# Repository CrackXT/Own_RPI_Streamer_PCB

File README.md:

# Own_RPI_Streamer_PCB

PCB files for RPI Streamer Board

# Description

This is a main board to hold a Raspberry Pi (4) and the Hifyberry Digi2 Pro expansion board. This puts the connections I need (for me) on one side to be able to build my own streamer.

- Part 1

The internal "power supply" (Pololu S13V30F5) delivers at 5V@3A, sensor and RGB are control by part 2.

There is a temperature sensor (Sensirion SHT45) under the SoC and an additional unregulated fan connector (e.g. Noctua NF-A4x20 5V). In addition there is the possibility to connect a lighting (RGB). Furthermore, the following connections are available... USB-C (power supply), USB-A 3.0 (data, e.g. USB stick with music on it), main switch, QWIIC/StemmaQT (sensor) and an external 5V connector (for part 2).

The board can be produced here (AISLER) with the files (.brd and .sch) or by any other PCB manufacturer. -> https://aisler.net/

# Spec

Vin: 2.8 - 22V<br>
Vout: 5V (typ., min.4,85V, max.5,15V)<br>
Iout: 3A<br>

# Serie

- .pro

# Layout

Top<br>

Bottom<br>

Routing/Dimensions(mm)<br>

Schematic<br>
Schematic as .pdf at the top of the page.

# License

Open hardware, use it, mod it, whatever you want, feel free...

# Thanks!

Own design and layout.

# Version - Build

v1.4 - 06.11.2023

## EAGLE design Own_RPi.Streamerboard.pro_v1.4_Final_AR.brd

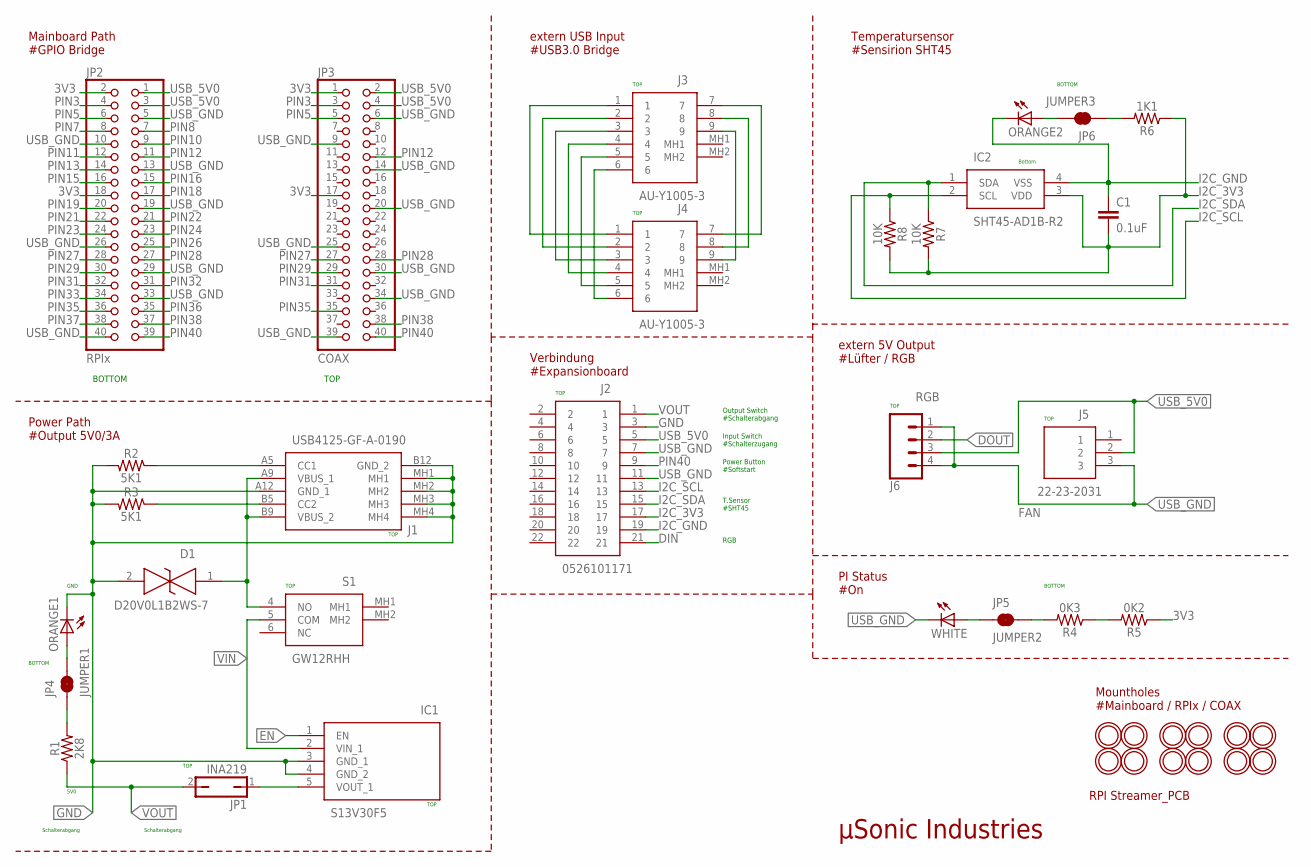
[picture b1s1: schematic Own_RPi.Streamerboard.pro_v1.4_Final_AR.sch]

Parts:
C1: 0.1uF; 0805
D1: D20V0L1B2WS-7; SOD2513X120N
IC1: S13V30F5
IC2: SHT45-AD1B-R2; SHT45AD1BR2
J1: USB4125-GF-A-0190; USB4125GFA0190
J2: 0526101171
J3, J4: AU-Y1005-3; AUY10053
J5: 22-23-2031; SHDR3W82P0X254_1X3_747X635X818
J6: CONN_041X04_NO_SILK; 1X04_NO_SILK
JP1: INA219; 1X02_NO_SILK
JP2: RPIx; 2X20-BIG
JP3: COAX; 2X20-BIG
JP4: JUMPER1; SMT-JUMPER_2_NC_TRACE_SILK
JP5: JUMPER2; SMT-JUMPER_2_NC_TRACE_SILK
JP6: JUMPER3; SMT-JUMPER_2_NC_TRACE_SILK
ORANGE1, ORANGE2: LEDCHIPLED_0805; CHIPLED_0805
R1: 2K8; 0805
R2, R3: 5K1; 0805
R4: 0K3; 0805
R5: 0K2; 0805
R6: 1K1; 0805
R7, R8: 10K; 0805
S1: GW12RHH
U$4, U$5, U$6, U$7, U$8, U$10, U$11, U$13, U$14, U$15, U$16, U$17: MOUNTINGHOLE2.5; MOUNTINGHOLE_2.5_PLATED
WHITE: LEDCHIPLED_0805; CHIPLED_0805

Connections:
3V3: JP2.2, JP2.18, JP3.1, JP3.17, R5.1
DIN: J2.21
DOUT: J6.2
EN: IC1.1 (EN)
GND: D1.2, IC1.3 (GND_1), IC1.4 (GND_2), J1.A12 (GND_1), J1.B12 (GND_2), J1.MH1, J1.MH2, J1.MH3, J1.MH4, J2.3, ORANGE1.C, R2.2, R3.2
I2C_3V3: C1.2, IC2.3 (VDD), J2.17, R6.1, R7.2, R8.2
I2C_GND: C1.1, IC2.4 (VSS), J2.19, ORANGE2.C
I2C_SCL: IC2.2 (SCL), J2.13, R8.1
I2C_SDA: IC2.1 (SDA), J2.15, R7.1
unnamed: JP4.1, R1.2
unnamed: R4.1, R5.2
unnamed: J1.B5 (CC2), R3.1
unnamed: J1.A5 (CC1), R2.1
unnamed: J3.4, J4.4
unnamed: JP6.2, ORANGE2.A
unnamed: JP5.1, WHITE.A
unnamed: IC1.5 (VOUT_1), JP1.1
unnamed: JP4.2, ORANGE1.A
unnamed: JP5.2, R4.2
unnamed: JP6.1, R6.2
unnamed: J3.6, J4.6
unnamed: J3.5, J4.5
unnamed: J3.3, J4.3
unnamed: J3.2, J4.2
unnamed: J3.1, J4.1
unnamed: J3.9, J4.9
unnamed: J3.8, J4.8
unnamed: J3.7, J4.7
PIN3: JP2.4, JP3.3
PIN5: JP2.6, JP3.5
PIN7: JP2.8
PIN8: JP2.7
PIN10: JP2.9
PIN11: JP2.12
PIN12: JP2.11, JP3.12
PIN13: JP2.14
PIN15: JP2.16
PIN16: JP2.15
PIN18: JP2.17
PIN19: JP2.20
PIN21: JP2.22
PIN22: JP2.21
PIN23: JP2.24
PIN24: JP2.23
PIN26: JP2.25
PIN27: JP2.28, JP3.27
PIN28: JP2.27, JP3.28
PIN29: JP2.30, JP3.29
PIN31: JP2.32, JP3.31
PIN32: JP2.31
PIN33: JP2.34
PIN35: JP2.36, JP3.35
PIN36: JP2.35
PIN37: JP2.38
PIN38: JP2.37, JP3.38
PIN40: J2.9, JP2.39, JP3.40
USB_5V0: J2.5, J5.2, J6.3, JP2.1, JP2.3, JP3.2, JP3.4
USB_GND: J2.7, J2.11, J5.3, J6.1, J6.4, JP2.5, JP2.10, JP2.13, JP2.19, JP2.26, JP2.29, JP2.33, JP2.40, JP3.6, JP3.9, JP3.14, JP3.20, JP3.25, JP3.30, JP3.34, JP3.39, WHITE.C
VBUS_VIN: D1.1, J1.A9 (VBUS_1), J1.B9 (VBUS_2), S1.4 (NO)
VIN: IC1.2 (VIN_1), S1.5 (COM)
VOUT: J2.1, JP1.2, R1.1

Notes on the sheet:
µSonic Industries
RPI Streamer_PCB
Power Path #Output 5V0/3A
TOP
Schalterabgang
BOTTOM
Mountholes #Mainboard / RPIx / COAX
GND
5V0
Temperatursensor #Sensirion SHT45
extern 5V Output #Lüfter / RGB
extern USB Input #USB3.0 Bridge
Mainboard Path #GPIO Bridge
PI Status #On
RGB
Bottom
Power Button #Softstart
Output Switch #Schalterabgang
Input Switch #Schalterzugang
T.Sensor #SHT45
Verbindung #Expansionboard
FAN

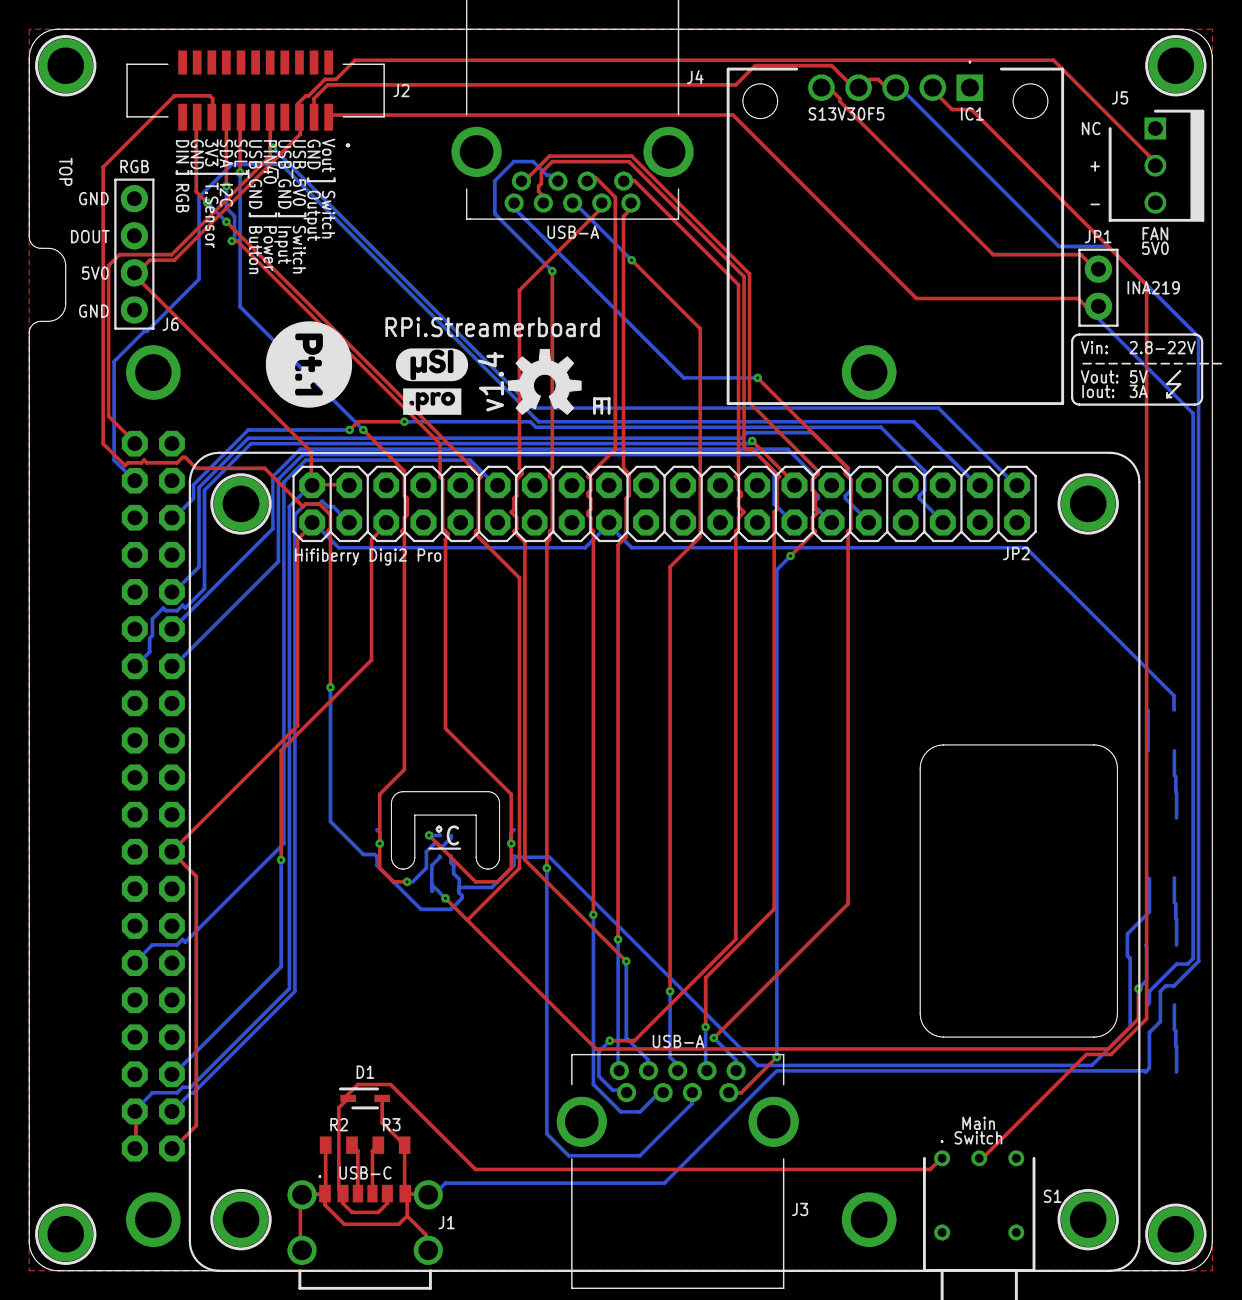
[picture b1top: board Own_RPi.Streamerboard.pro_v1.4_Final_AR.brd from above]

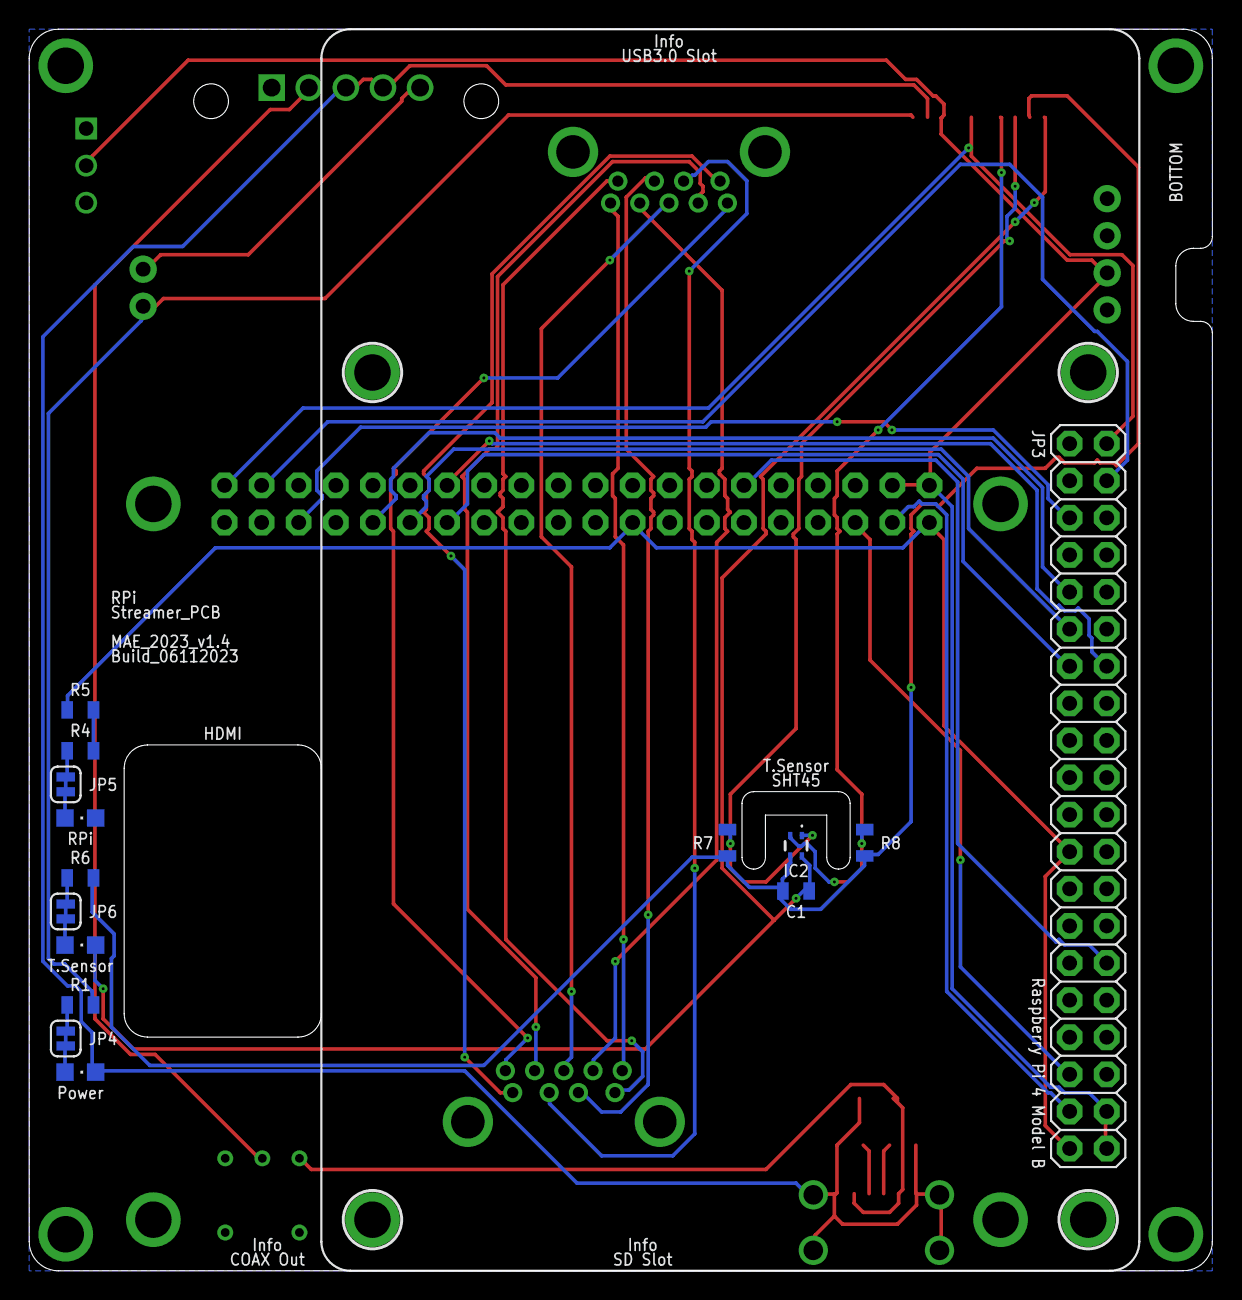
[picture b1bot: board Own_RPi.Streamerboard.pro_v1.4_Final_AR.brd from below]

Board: 2 copper layers, 81.0 x 85.0 mm, 44 parts (19 on the bottom side), 40 nets.

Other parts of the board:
U$1: .PRO_LARGE
U$2: OSHW-LOGO-M
U$3: PT.1
U$18: µSI_LARGE

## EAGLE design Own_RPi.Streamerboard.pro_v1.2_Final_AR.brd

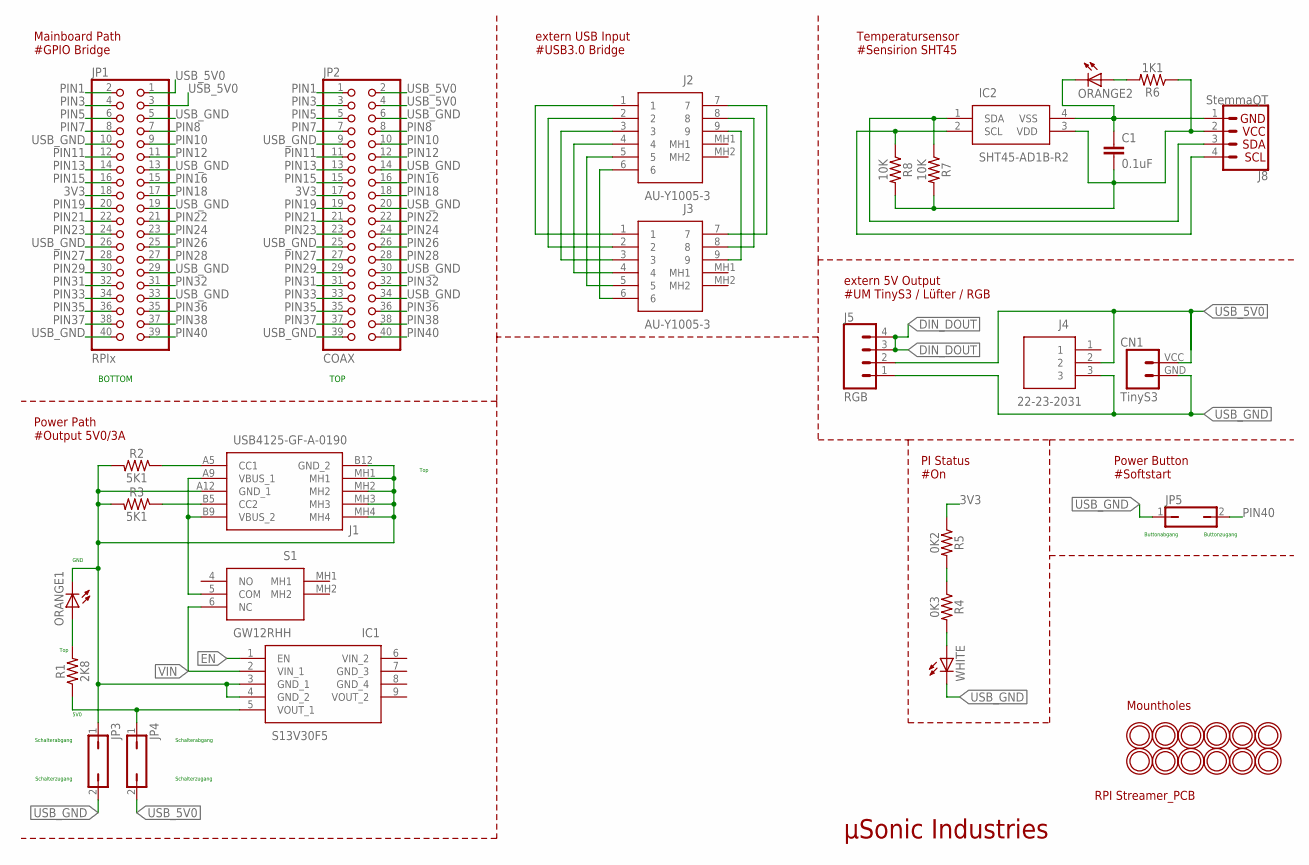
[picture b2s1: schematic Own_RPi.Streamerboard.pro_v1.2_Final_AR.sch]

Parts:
C1: 0.1uF; 0805
CN1: TinyS3; JST-2-SMD-VERT
IC1: S13V30F5
IC2: SHT45-AD1B-R2; SHT45AD1BR2
J1: USB4125-GF-A-0190; USB4125GFA0190
J2, J3: AU-Y1005-3; AUY10053
J4: 22-23-2031; SHDR3W82P0X254_1X3_747X635X818
J5: RGB; 1X04
J8: StemmaQT; JST04_1MM_VERT
JP1: RPIx; 2X20-BIG
JP2: COAX; 2X20-BIG
JP3, JP4, JP5: JP1Q; JP1
ORANGE1, ORANGE2: LEDCHIPLED_0805; CHIPLED_0805
R1: 2K8; 0805
R2, R3: 5K1; 0805
R4: 0K3; 0805
R5: 0K2; 0805
R6: 1K1; 0805
R7, R8: 10K; 0805
S1: GW12RHH
U$3, U$5, U$8, U$9, U$10, U$11, U$12, U$13, U$14, U$15, U$16, U$17: MOUNTINGHOLE2.5; MOUNTINGHOLE_2.5_PLATED
WHITE: LEDCHIPLED_0805; CHIPLED_0805

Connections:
3V3: JP1.18, JP2.17, R5.1
DIN_DOUT: J5.3, J5.4
EN: IC1.1 (EN)
GND: IC1.3 (GND_1), IC1.4 (GND_2), J1.A12 (GND_1), J1.B12 (GND_2), J1.MH1, J1.MH2, J1.MH3, J1.MH4, JP3.1, ORANGE1.C, R2.2, R3.2
unnamed: ORANGE1.A, R1.2
unnamed: R4.1, R5.2
unnamed: J1.B5 (CC2), R3.1
unnamed: J1.A5 (CC1), R2.1
unnamed: J2.4, J3.4
unnamed: ORANGE2.A, R6.2
unnamed: R4.2, WHITE.A
unnamed: C1.2, IC2.3 (VDD), J8.2, R6.1, R7.2, R8.2
unnamed: C1.1, IC2.4 (VSS), J8.1, ORANGE2.C
unnamed: IC2.2 (SCL), J8.4, R8.1
unnamed: J2.6, J3.6
unnamed: IC2.1 (SDA), J8.3, R7.1
unnamed: J2.5, J3.5
unnamed: J2.3, J3.3
unnamed: J2.2, J3.2
unnamed: J2.1, J3.1
unnamed: J2.9, J3.9
unnamed: J2.8, J3.8
unnamed: J2.7, J3.7
PIN1: JP1.2, JP2.1
PIN3: JP1.4, JP2.3
PIN5: JP1.6, JP2.5
PIN7: JP1.8, JP2.7
PIN8: JP1.7, JP2.8
PIN10: JP1.9, JP2.10
PIN11: JP1.12, JP2.11
PIN12: JP1.11, JP2.12
PIN13: JP1.14, JP2.13
PIN15: JP1.16, JP2.15
PIN16: JP1.15, JP2.16
PIN18: JP1.17, JP2.18
PIN19: JP1.20, JP2.19
PIN21: JP1.22, JP2.21
PIN22: JP1.21, JP2.22
PIN23: JP1.24, JP2.23
PIN24: JP1.23, JP2.24
PIN26: JP1.25, JP2.26
PIN27: JP1.28, JP2.27
PIN28: JP1.27, JP2.28
PIN29: JP1.30, JP2.29
PIN31: JP1.32, JP2.31
PIN32: JP1.31, JP2.32
PIN33: JP1.34, JP2.33
PIN35: JP1.36, JP2.35
PIN36: JP1.35, JP2.36
PIN37: JP1.38, JP2.37
PIN38: JP1.37, JP2.38
PIN40: JP1.39, JP2.40, JP5.2
USB_5V0: CN1.VCC (2), J4.2, J5.2, JP1.1, JP1.3, JP2.2, JP2.4, JP4.2
USB_GND: CN1.GND (1), J4.3, J5.1, JP1.5, JP1.10, JP1.13, JP1.19, JP1.26, JP1.29, JP1.33, JP1.40, JP2.6, JP2.9, JP2.14, JP2.20, JP2.25, JP2.30, JP2.34, JP2.39, JP3.2, JP5.1, WHITE.C
VBUS_VIN: J1.A9 (VBUS_1), J1.B9 (VBUS_2), S1.5 (COM)
VIN: IC1.2 (VIN_1), S1.6 (NC)
VOUT: IC1.5 (VOUT_1), JP4.1, R1.1

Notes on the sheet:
µSonic Industries
RPI Streamer_PCB
Power Path #Output 5V0/3A
Top
Schalterabgang
Mountholes
GND
5V0
TOP
BOTTOM
Temperatursensor #Sensirion SHT45
extern 5V Output #UM TinyS3 / Lüfter / RGB
extern USB Input #USB3.0 Bridge
Mainboard Path #GPIO Bridge
Power Button #Softstart
PI Status #On
Schalterzugang
Buttonzugang
Buttonabgang
RGB

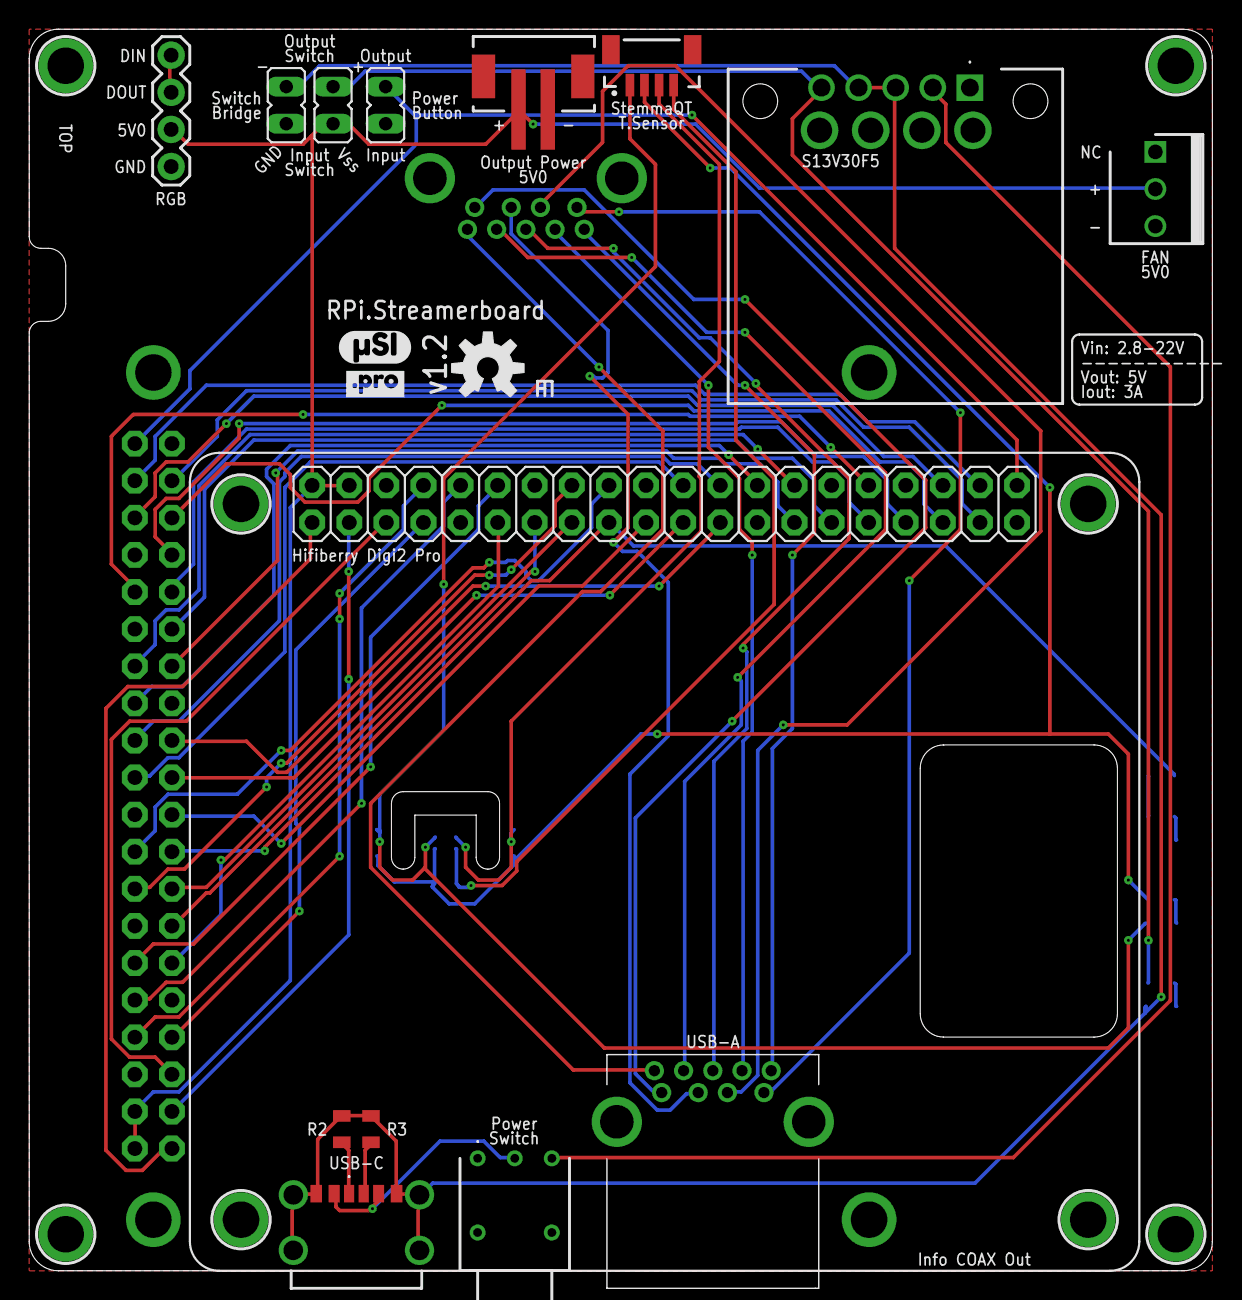
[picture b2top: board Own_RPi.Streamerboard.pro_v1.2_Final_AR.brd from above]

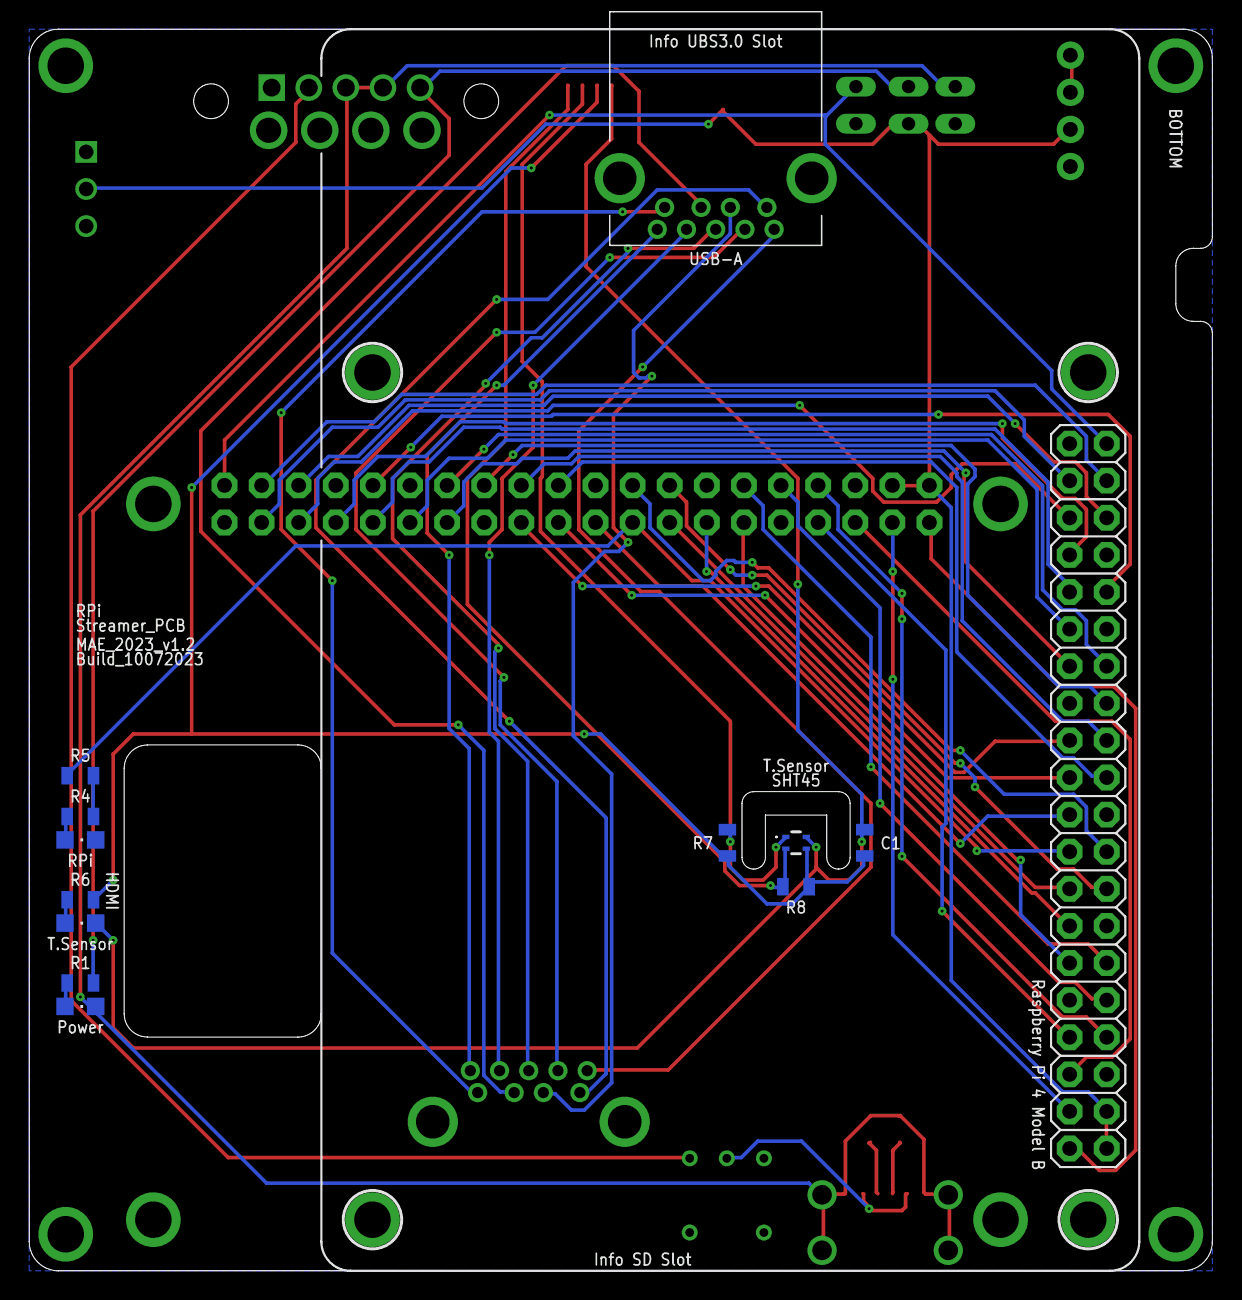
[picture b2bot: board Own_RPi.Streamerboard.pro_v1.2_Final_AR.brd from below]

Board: 2 copper layers, 81.0 x 85.0 mm, 42 parts (17 on the bottom side), 56 nets.

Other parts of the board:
U$1: .PRO_LARGE
U$2: OSHW-LOGO-M
U$18: µSI_LARGE

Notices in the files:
parts and their libraries:
microbuilder: This work is placed in the public domain, and may be freely used for commercial and non-commercial work with the following conditions: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
SparkFun-Aesthetics: Licensing: Creative Commons ShareAlike 4.0 International - https://creativecommons.org/licenses/by-sa/4.0
